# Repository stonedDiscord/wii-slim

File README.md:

# wii-slim
## WIP

This OpenSCAD project tries to model the 3 parts of the Nintendo Wii Case for 3D printing.

Currently only the top case is modelled, and the goal is end up with a "Wii Slim".
For this, the disk drive is removed and the top shell is replaced with a modified 3D printed one.

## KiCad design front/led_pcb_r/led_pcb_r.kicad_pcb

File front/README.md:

# wii-slim
## front

This folder contains the files for the front plate, SD card door and all the buttons.

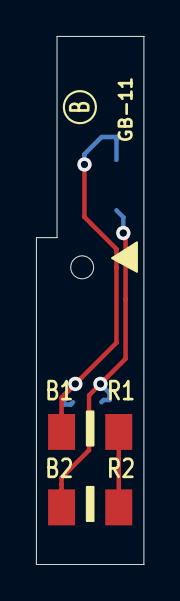
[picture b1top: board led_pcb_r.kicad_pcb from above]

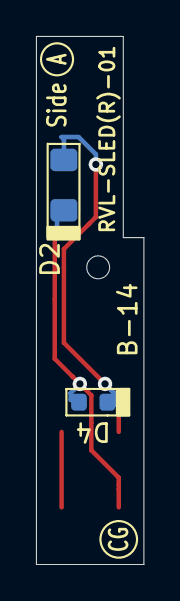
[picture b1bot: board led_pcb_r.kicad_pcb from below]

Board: 2 copper layers, 6.0 x 29.3 mm, 6 parts (2 on the bottom side), 3 nets.

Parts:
B1, B2: TestPoint; TestPoint_Pad_1.5x1.5mm
D2: LED; LED_1206_3216Metric
D4: D; D_0603_1608Metric
R1, R2: TestPoint; TestPoint_Pad_1.5x1.5mm

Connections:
unnamed: B1.1, D2.1, D4.2
unnamed: B2.1, D2.2, D4.1
unnamed: R1.1, R2.1

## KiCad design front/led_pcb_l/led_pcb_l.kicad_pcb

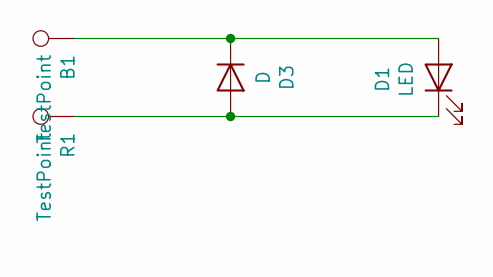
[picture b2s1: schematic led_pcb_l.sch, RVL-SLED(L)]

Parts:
B1: TestPoint; TestPoint_Pad_1.5x1.5mm
D1: LED; LED_1206_3216Metric
D3: D; D_0603_1608Metric
R1: TestPoint; TestPoint_Pad_1.5x1.5mm

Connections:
unnamed: B1.1, D1.2 (A), D3.1 (K)
unnamed: D1.1 (K), D3.2 (A), R1.1

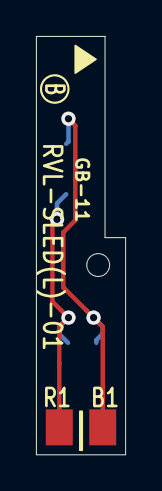
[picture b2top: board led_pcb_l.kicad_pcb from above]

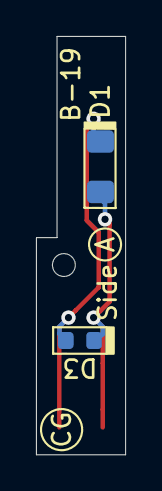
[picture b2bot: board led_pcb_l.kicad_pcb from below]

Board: 2 copper layers, 5.0 x 23.2 mm, 4 parts (2 on the bottom side), 2 nets.

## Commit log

2020-01-12 add OpenSCAD gitignore
2020-01-12 simply fan grille
2020-01-12 rename standoff, change memcard
2020-01-12 add fan and option to disable one gc mem slot
2020-01-12 missing fan position
2020-01-12 shield standoffs optional
2020-01-12 add front lip screwholes
2020-01-12 flip screws on the right side
2020-01-12 move screwposts and standoffs
2020-01-13 move connector standoffs
2020-01-13 adjust case width after test print turned out too small
2020-01-13 ac supports were loose
2020-01-13 wrong connector side thickness
2020-01-13 adjust battery and move front lip
2020-01-13 move foot
2020-01-13 change screwholes and make them recessed
2020-01-13 acurate model for the controller port
2020-01-13 add case screw posts supports
2020-01-13 only include this foot if it has something to hold onto
2020-01-13 more multi-out
2020-01-13 get rid of foot part floating in the air
2020-01-13 add ac connector outer standoffs
2020-01-13 adjust depth of some elements
2020-01-13 finish sensorbar
2020-01-13 this was a little off
2020-01-13 remove flicker and make it 2manifold
2020-01-13 Add a render for the readme
2020-01-14 fix flicker on standoffs and widen usb
2020-01-14 make ac fit better
2020-01-14 move screwhole
2020-01-14 fix gc port spacing
2020-01-16 finished dust filter
2020-01-16 image of dust filter
2020-01-16 got my hands on a front cover
2020-01-16 start work on slot light
    (even though i won't need it anymore)
2020-01-17 add button template and reset button
2020-01-17 add light holder to front
2020-01-17 add sync button and mount points
2020-01-17 add button angles and sd border
2020-01-17 add disk slot
2020-01-17 get the shape right
2020-01-18 add slots for door clips
2020-01-21 add power button
2020-01-21 work on holder
2020-01-21 looks better
2020-01-22 change folder structure
2020-01-24 add scans of the stand
2020-01-24 add gitignore for pcbs
2020-01-24 add LED PCBs
2020-01-24 add scan and render of front
2020-01-24 add scans of the led pcbs
2020-01-24 adjust left pcb
2020-01-24 adjust right pcb
2020-01-24 move files around to make more sense
2020-02-17 add supports around the screwholes and for the flaps
2020-02-17 forgot right side
2020-02-17 need to rethink the angle
2020-02-17 add comments, move sd part into own module
2020-02-28 the height was wrong and i had a syntax error causing the screwposts to disappear
2020-02-28 undo mistakes on the battery holder
2020-02-28 calculate width and height based on the wall thickness, adjust buttons
2020-02-28 account wall thickness in button positions
2020-03-08 there was a gap
2020-03-08 add slope in sd door
2020-03-08 simplyfy sd door
2020-03-09 make the variables customizer friendly
2020-03-09 seperate slots and buttons in customizer
2020-03-09 parameterize the shell
2020-03-09 parameterize dust filter
2020-07-20 finish the slot lightpipe
